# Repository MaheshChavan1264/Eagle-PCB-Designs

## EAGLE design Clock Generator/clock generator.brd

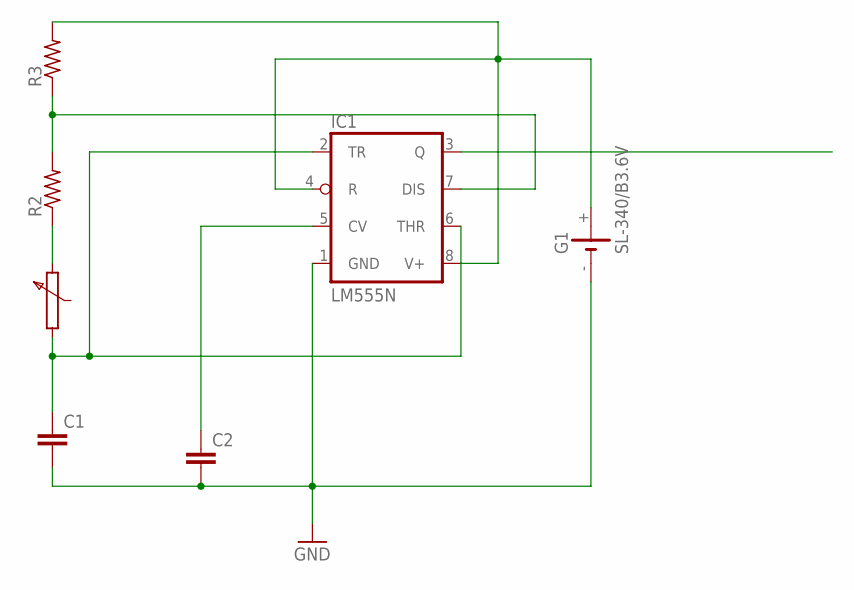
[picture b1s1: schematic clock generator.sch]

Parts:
C1, C2: C2,5-3; C2.5-3
G1: SL-340/B3.6V
IC1: LM555N; DIL08-ROUND
R2, R3: R-US_0204/7; 0204/7

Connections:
GND: C1.2, C2.2, G1.-, IC1.1 (GND)
unnamed: G1.+, IC1.4 (R), IC1.8 (V+), R3.2
unnamed: C1.1, IC1.2 (TR), IC1.6 (THR)
unnamed: C2.1, IC1.5 (CV)
unnamed: IC1.7 (DIS), R2.2, R3.1

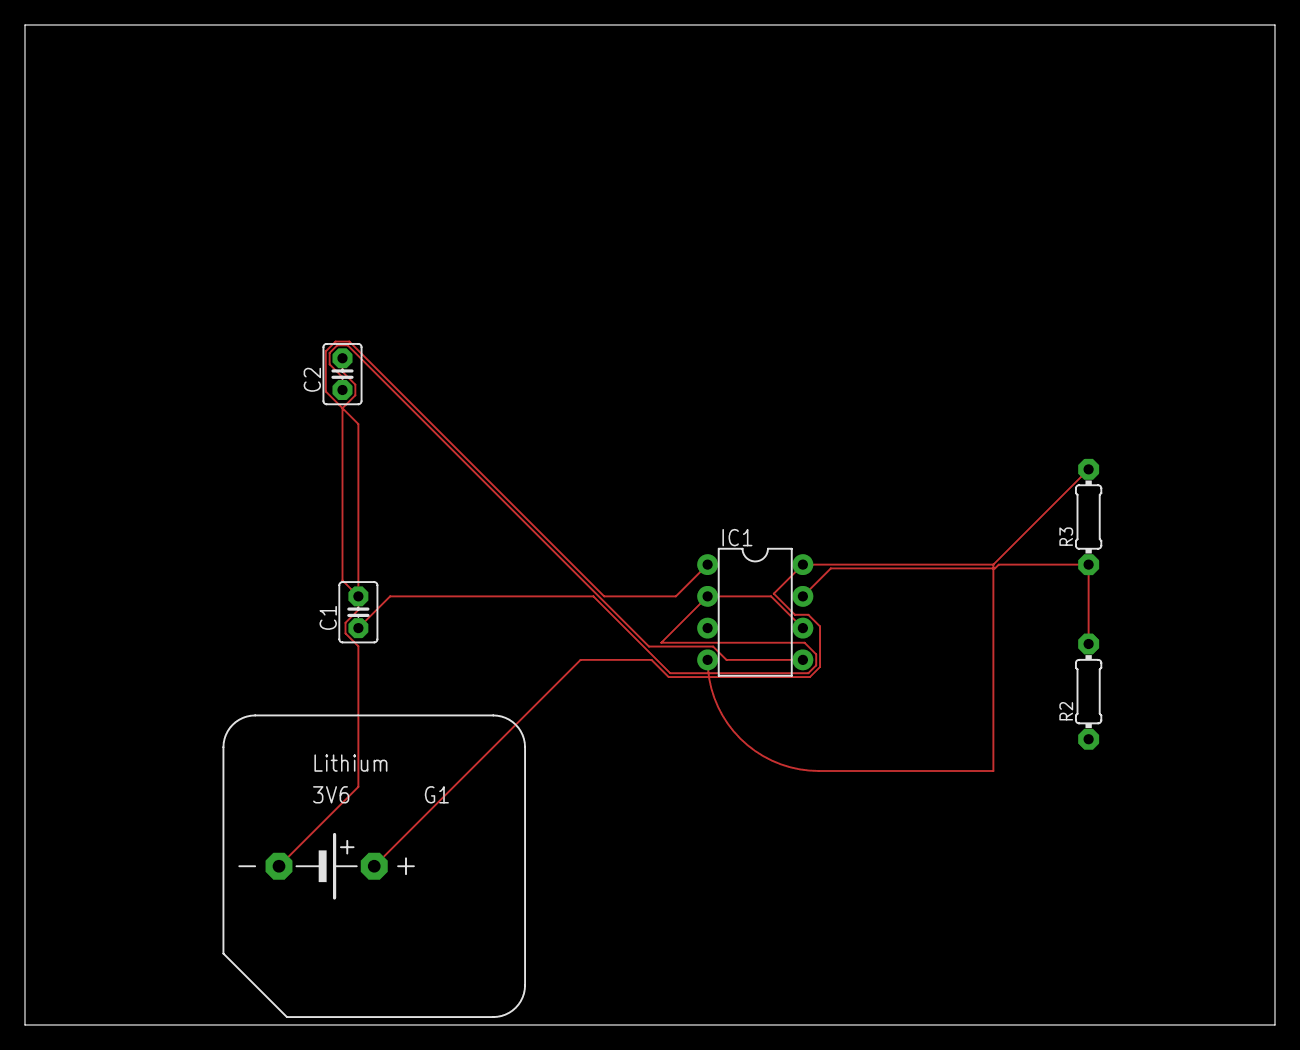
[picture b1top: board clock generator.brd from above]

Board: 2 copper layers, 100.0 x 80.0 mm, 6 parts (0 on the bottom side), 5 nets.

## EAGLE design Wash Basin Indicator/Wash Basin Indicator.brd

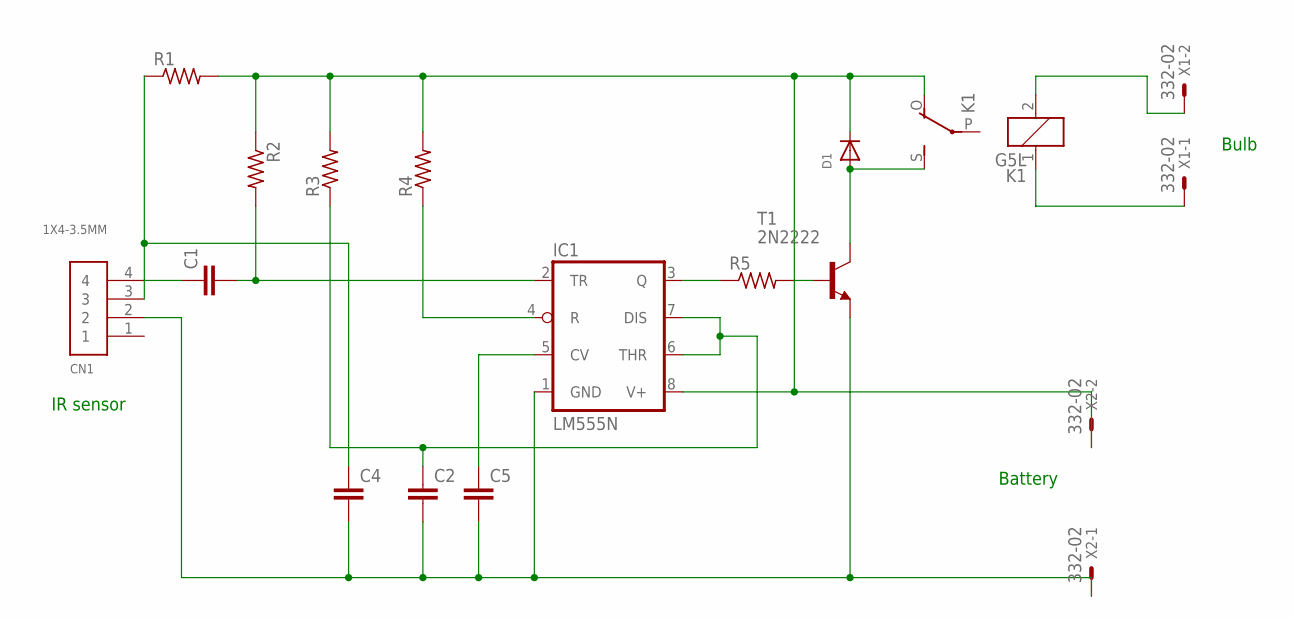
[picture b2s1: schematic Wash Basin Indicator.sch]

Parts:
C1, C2, C4, C5: C5/3.5; C5B3.5
CN1: 1X4-3.5MM; 1X04-3.5MM
D1: DIODEDO-1N4148; DO-1N4148
IC1: LM555N; DIL08
K1: G5L; G5LE
R1, R2, R3, R4, R5: R-US_0204/7; 0204/7
T1: 2N2222; TO92-EBC-OVAL
X1, X2: 332-02

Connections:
unnamed: D1.C, IC1.8 (V+), K1.O, R1.2, R2.1, R3.2, R4.2, X2.2
unnamed: IC1.4 (R), R4.1
unnamed: C1.2, IC1.2 (TR), R2.2
unnamed: C1.1, CN1.4
unnamed: C2.2, C4.2, C5.2, CN1.2, IC1.1 (GND), T1.E, X2.1
unnamed: C4.1, CN1.3, R1.1
unnamed: IC1.3 (Q), R5.1
unnamed: R5.2, T1.B
unnamed: D1.A, K1.S, T1.C
unnamed: C5.1, IC1.5 (CV)
unnamed: K1.2, X1.2
unnamed: C2.1, IC1.6 (THR), IC1.7 (DIS), R3.1
unnamed: K1.1, X1.1

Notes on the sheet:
IR sensor
Battery
Bulb

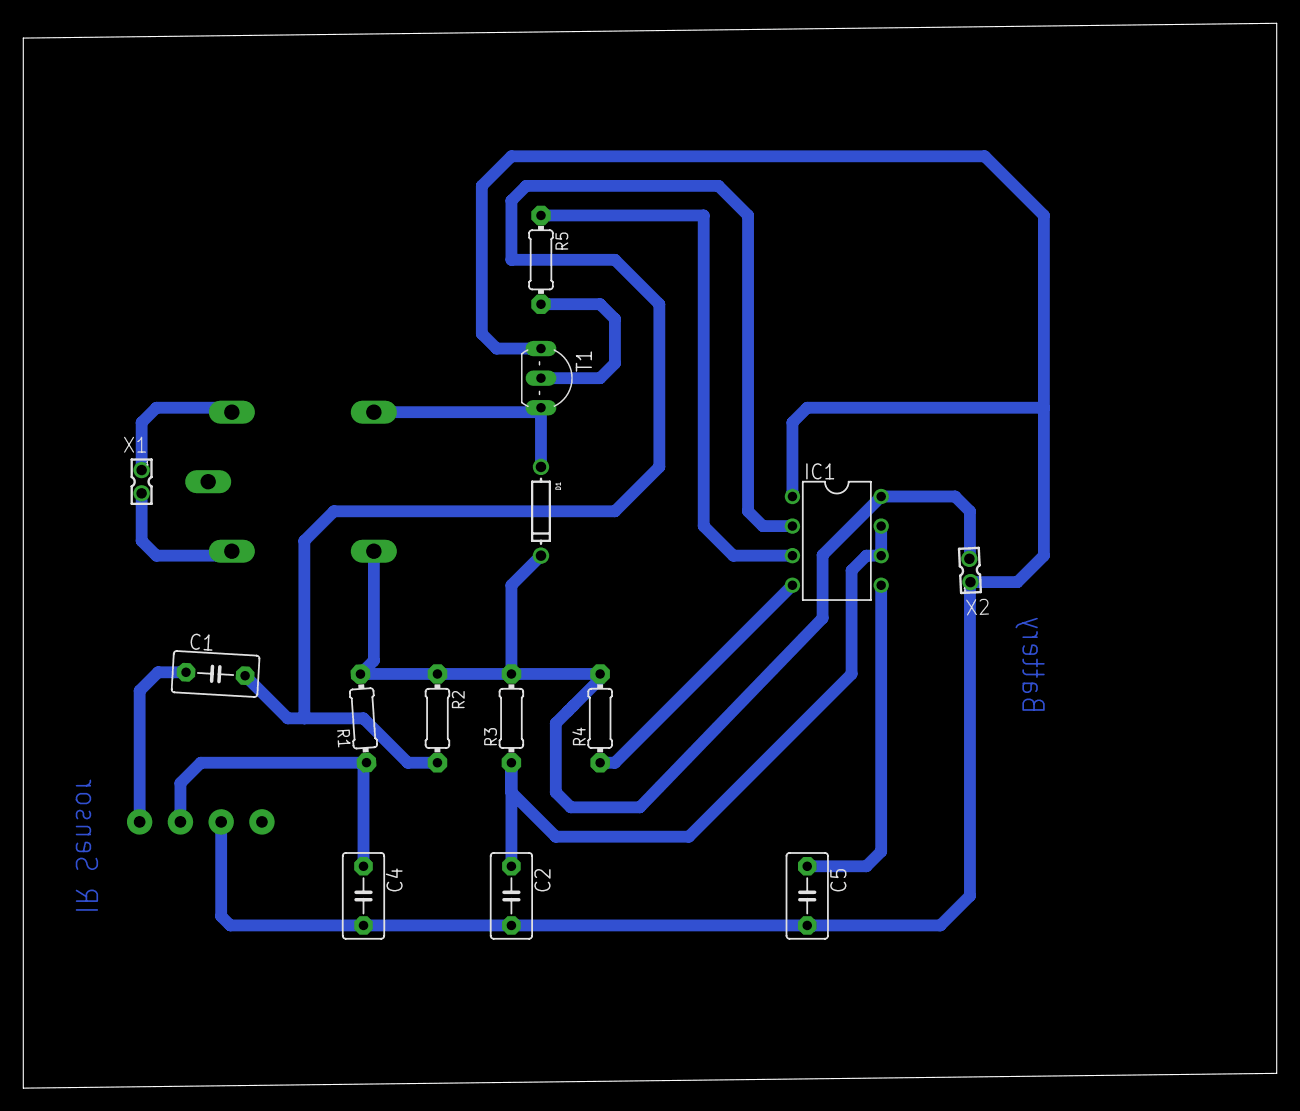
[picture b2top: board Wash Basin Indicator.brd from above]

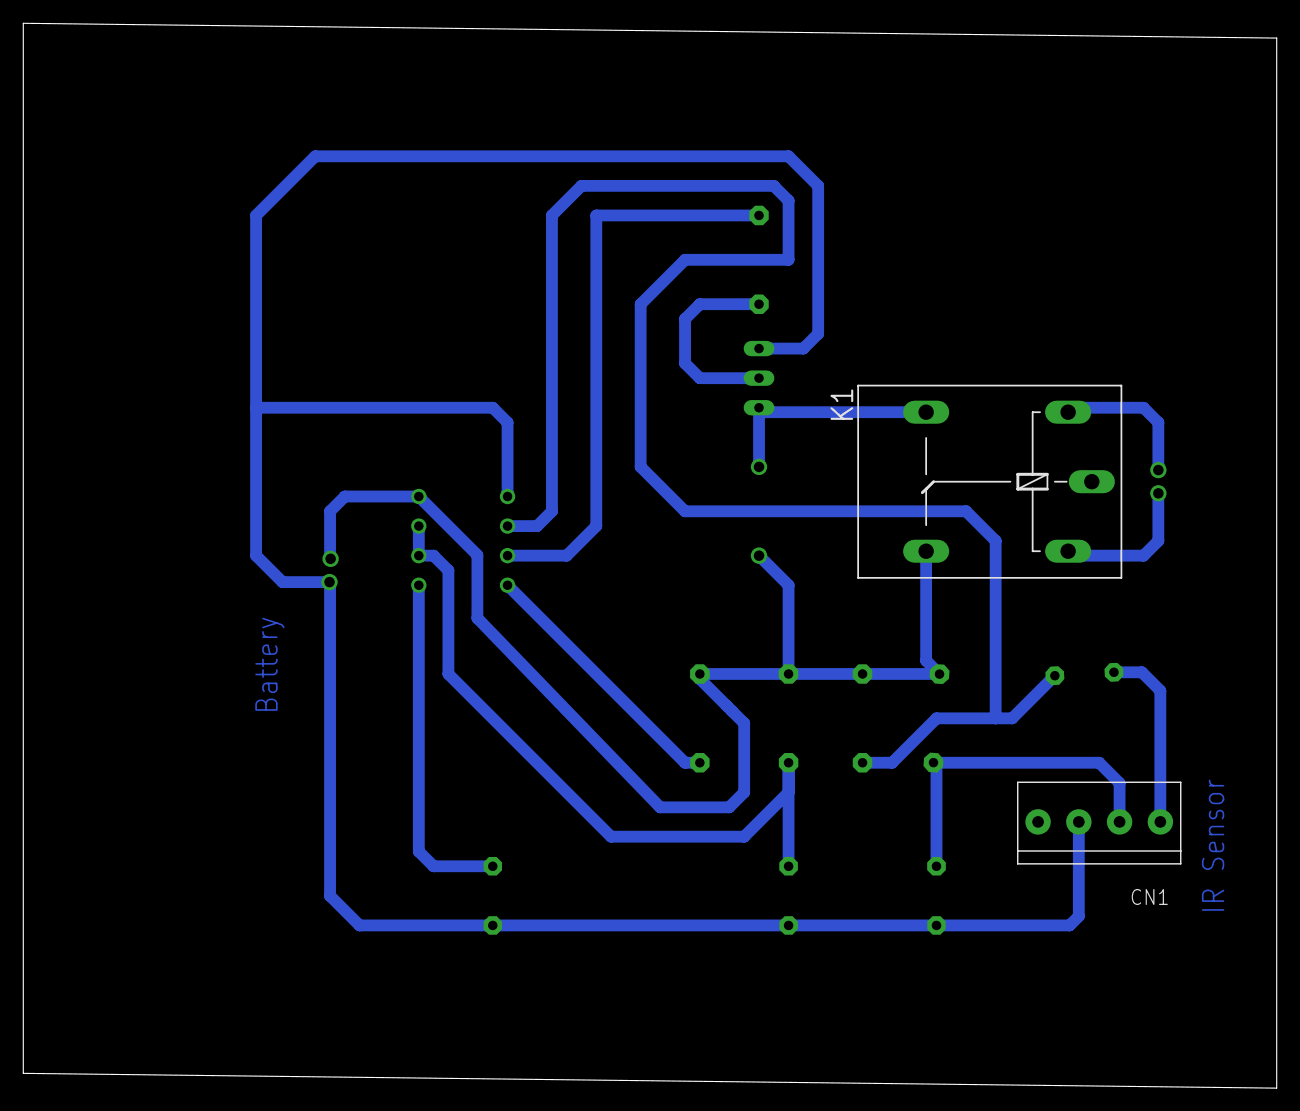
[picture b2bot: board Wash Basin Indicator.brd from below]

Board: 2 copper layers, 107.6 x 91.4 mm, 16 parts (2 on the bottom side), 13 nets.

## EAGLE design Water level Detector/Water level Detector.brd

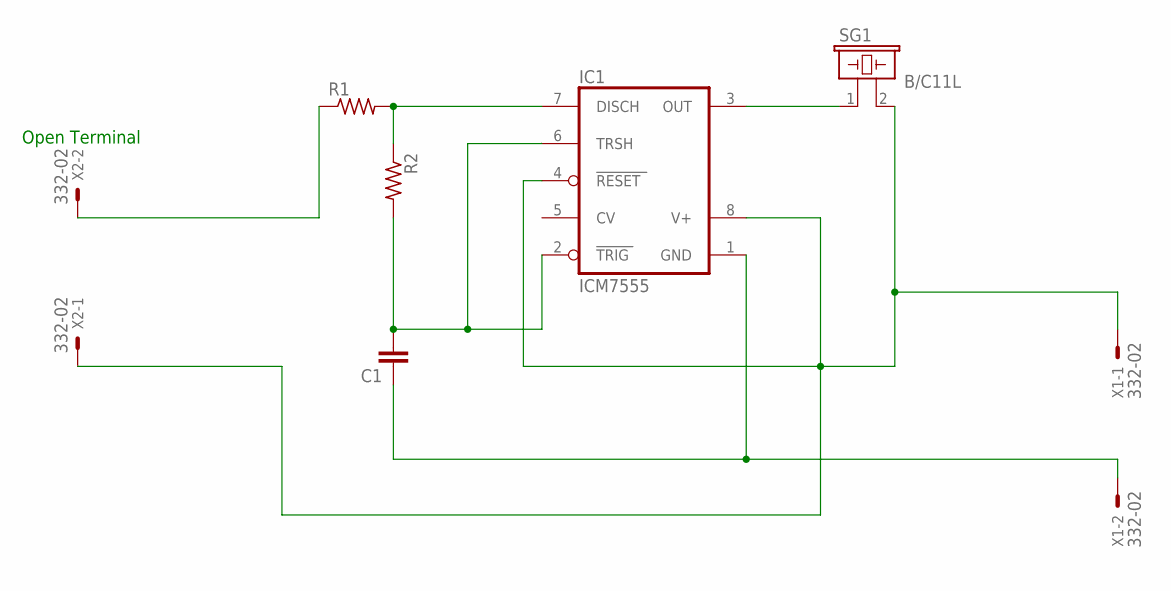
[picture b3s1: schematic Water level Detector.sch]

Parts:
C1: C5/2.5; C5B2.5
IC1: ICM7555; DIL08
R1, R2: R-US_0204/7; 0204/7
SG1: B/C11L
X1, X2: 332-02

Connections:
unnamed: IC1.7 (DISCH), R1.2, R2.1
unnamed: C1.2, IC1.2 (TRIG), IC1.6 (TRSH), R2.2
unnamed: R1.1, X2.2
unnamed: IC1.4 (RESET), IC1.8 (V+), SG1.2, X1.1, X2.1
unnamed: C1.1, IC1.1 (GND), X1.2
unnamed: IC1.3 (OUT), SG1.1

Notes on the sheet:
Open Terminal

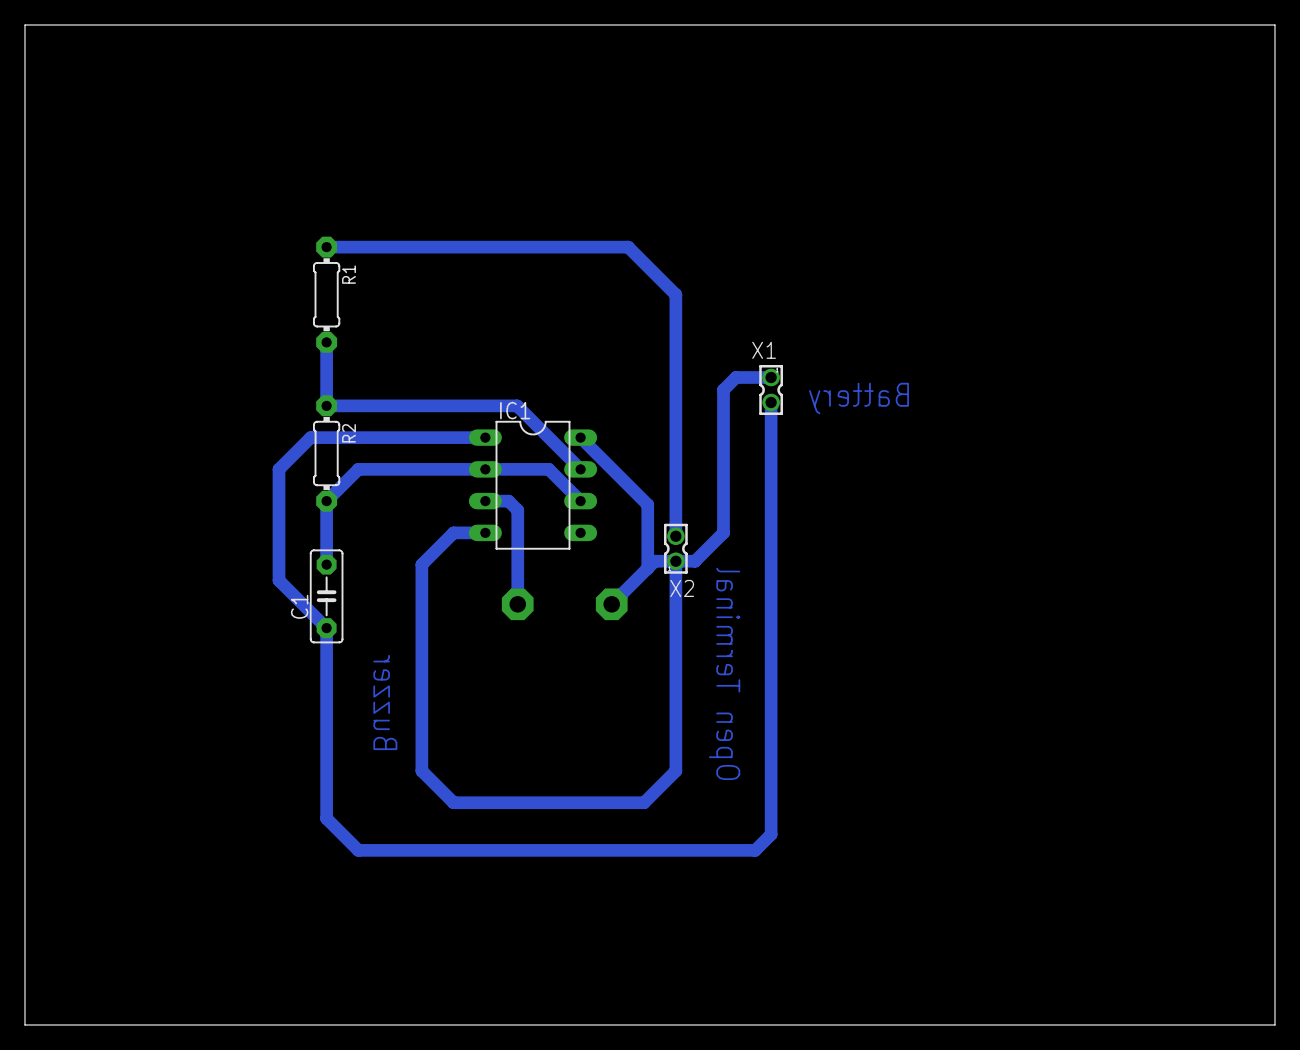
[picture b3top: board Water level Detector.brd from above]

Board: 2 copper layers, 100.0 x 80.0 mm, 7 parts (1 on the bottom side), 6 nets.

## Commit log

2019-03-31 Eagle Designs
